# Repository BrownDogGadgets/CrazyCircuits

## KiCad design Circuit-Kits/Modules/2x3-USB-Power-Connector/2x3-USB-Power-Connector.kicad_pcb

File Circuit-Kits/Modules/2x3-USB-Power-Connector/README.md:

<!--- start title --->
# 2x3 USB Power Connector Module v1.1
A Lego-compatible Crazy Circuits module

- Updated: 27 May 2017
- Website: http://browndoggadgets.com/
- Company: Brown Dog Gadgets
- License: CERN Open Hardware License v1.2.

<!--- end title --->
Micro-USB connector edge piece that breaks out 3.3V from the USB 5V along with the GND. This could be used instead of a coin cell battery.

<!--- bom start --->
### Bill of Materials

|Ref|Qty|Description|Digikey PN|
|---|---|-----------|------|
|C1 C2|2|CAP CER 1UF 25V X7R 0603|587-2984-1-ND|
|J1|1|USB MICRO-B RECEPTACLE 5PIN SMT R/A STUDS|609-4616-1-ND|
|U1|1|IC REG LDO 3.3V 0.15A SOT353|576-3193-1-ND|

<!--- bom end --->

### Manufacturing Notes

This board must be v-scored. Do not panelize with support tabs or mousebites.

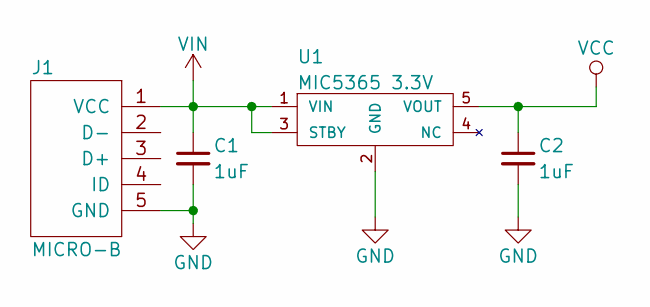
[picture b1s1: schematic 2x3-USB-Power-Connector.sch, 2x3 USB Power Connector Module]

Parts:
C1, C2: 1uF; RLC-0603-SMD
J1: MICRO-B; CONN-USB-MICRO-B-AMPHENOL-10118193-0001LF
U1: MIC5365 3.3V; SOT-353

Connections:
GND: C1.2, C2.2, J1.5 (GND), U1.2 (GND)
VCC: C2.1, U1.5 (VOUT)
VIN: C1.1, J1.1 (VCC), U1.1 (VIN), U1.3 (STBY)

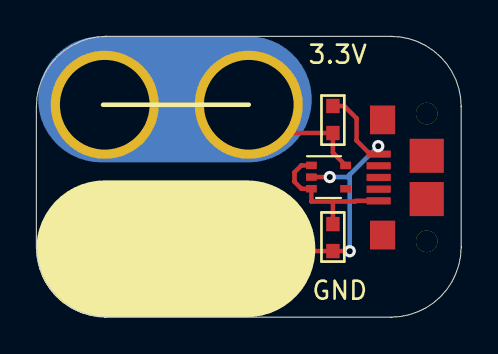
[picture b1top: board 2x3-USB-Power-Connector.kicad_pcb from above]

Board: 2 copper layers, 23.6 x 15.6 mm, 5 parts (0 on the bottom side), 3 nets.

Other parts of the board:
J1#2: MICRO-B; USB-CONNECTOR-2x3
